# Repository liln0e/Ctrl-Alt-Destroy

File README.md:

# Ctrl+Alt+Destroy

<p align="center">
  <b>BattleBot de tipo sumo diseñado y construido por el equipo Ctrl+Alt+Destroy</b><br>
  Grado en Robótica · Escola Politécnica Superior de Enxeñaría (EPSE) · USC<br>
  Asignatura: <a href="https://www.usc.gal/es/estudios/grados/ingenieria-arquitectura/grado-robotica-2a-edicion/20252026/tecnologia-electrica-19946-19042-2-105699">Tecnología eléctrica</a>
</p>

<p align="center">
  <a href="https://www.youtube.com/live/FVRY-8WoZKk">▶ Ver la batalla</a> ·
  <a href="https://liln0e.github.io/Ctrl-Alt-Destroy/">Web del proyecto</a> ·
  <a href="https://battlebots.robotica.gal/Ctrl-Alt-Destroy/">Web oficial (battlebots.robotica.gal)</a>
</p>

---

## Descripción

**Ctrl+Alt+Destroy** es un robot BattleBot desarrollado como proyecto de la asignatura **Tecnología eléctrica** del Grado en Robótica. Junta electrónica, modelado e impresión 3D, programación y documentación técnica en un robot funcional que compitió en el torneo de la asignatura.

- **Electrónica:** PCB propia diseñada en KiCad, con una ESP32 como controlador principal.
- **Mecánica:** chasis y tapa modelados e impresos en 3D.
- **Software:** código Arduino para el control de motores, la lectura de sensores y la lógica de combate.
- **Documentación:** web hecha con Jekyll, con documentación técnica, costes y fotos del proceso.

## Estructura del repositorio

```txt
Ctrl-Alt-Destroy/
├── README.md
├── LICENSE
├── electronica/   → Esquemático y PCB en KiCad
├── mecanica/      → Modelos 3D (.3mf) y G-code del chasis y la tapa
├── software/      → Código del robot (sumo_robot_final.ino)
└── web/           → Web de documentación (Jekyll)
```

Documentación detallada en la web:

- [Documentación técnica](web/documentacion.md)
- [Costes](web/costes.md)
- [Fotos del proceso](web/fotos.md)

## Equipo

| Integrante | Rol |
|---|---|
| **Carmen Sestelo Arias** · [@carmensesteloarias](https://github.com/carmensesteloarias) | Electrónica, diseño de la PCB, código y construcción del robot |
| **Brais Maciñeiras Pena** · [@braisiiito](https://github.com/braisiiito) | Modelado e impresión 3D del chasis, código y coordinación |
| **Noelia Castro Rodríguez** · [@liln0e](https://github.com/liln0e) | Repositorio, web, documentación y decoración del robot |

## Ver la web en local

```bash
bundle install
bundle exec jekyll serve --source web
```

## Licencia

Proyecto académico publicado bajo la [licencia MIT](./LICENSE).

## Sobre este repositorio

Esta es una copia del repositorio oficial del equipo, que está en GitLab (`epse-usc/Ctrl-Alt-Destroy`), con su historial completo. Aquí la web se publica en GitHub Pages con [`.github/workflows/pages.yml`](.github/workflows/pages.yml). El archivo `.gitlab-ci.yml` se mantiene porque es el que usa el repositorio oficial.

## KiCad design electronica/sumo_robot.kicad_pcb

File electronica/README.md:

# Diseño electrónico del robot

En esta carpeta se incluye la documentación electrónica necesaria para el desarrollo del robot BattleBot del equipo **Ctrl+Alt+Destroy**.

## Contenido

Los siguientes archivos corresponden al diseño electrónico realizado en **KiCad**:

- `sumo_robot.kicad_sch` → Esquemático electrónico del circuito.
- `sumo_robot.kicad_pcb` → Diseño de la PCB del robot.
- `sumo_robot.kicad_pro` → Archivo del proyecto de KiCad.

## Diseño electrónico

La PCB ha sido diseñada para integrar los componentes electrónicos necesarios para el funcionamiento del robot, incluyendo:

- Alimentación del sistema.
- Integración del microcontrolador ESP32.
- Conexiones para sensores.
- Control de actuadores y elementos electrónicos del robot.

El diseño electrónico se ha realizado utilizando **KiCad**, permitiendo la organización de conexiones, distribución de componentes y fabricación de una PCB personalizada.

Las imágenes del diseño de la PCB y de la placa fabricada pueden consultarse en la documentación web del proyecto.

**Responsable principal:** Carmen Sestelo Arias.

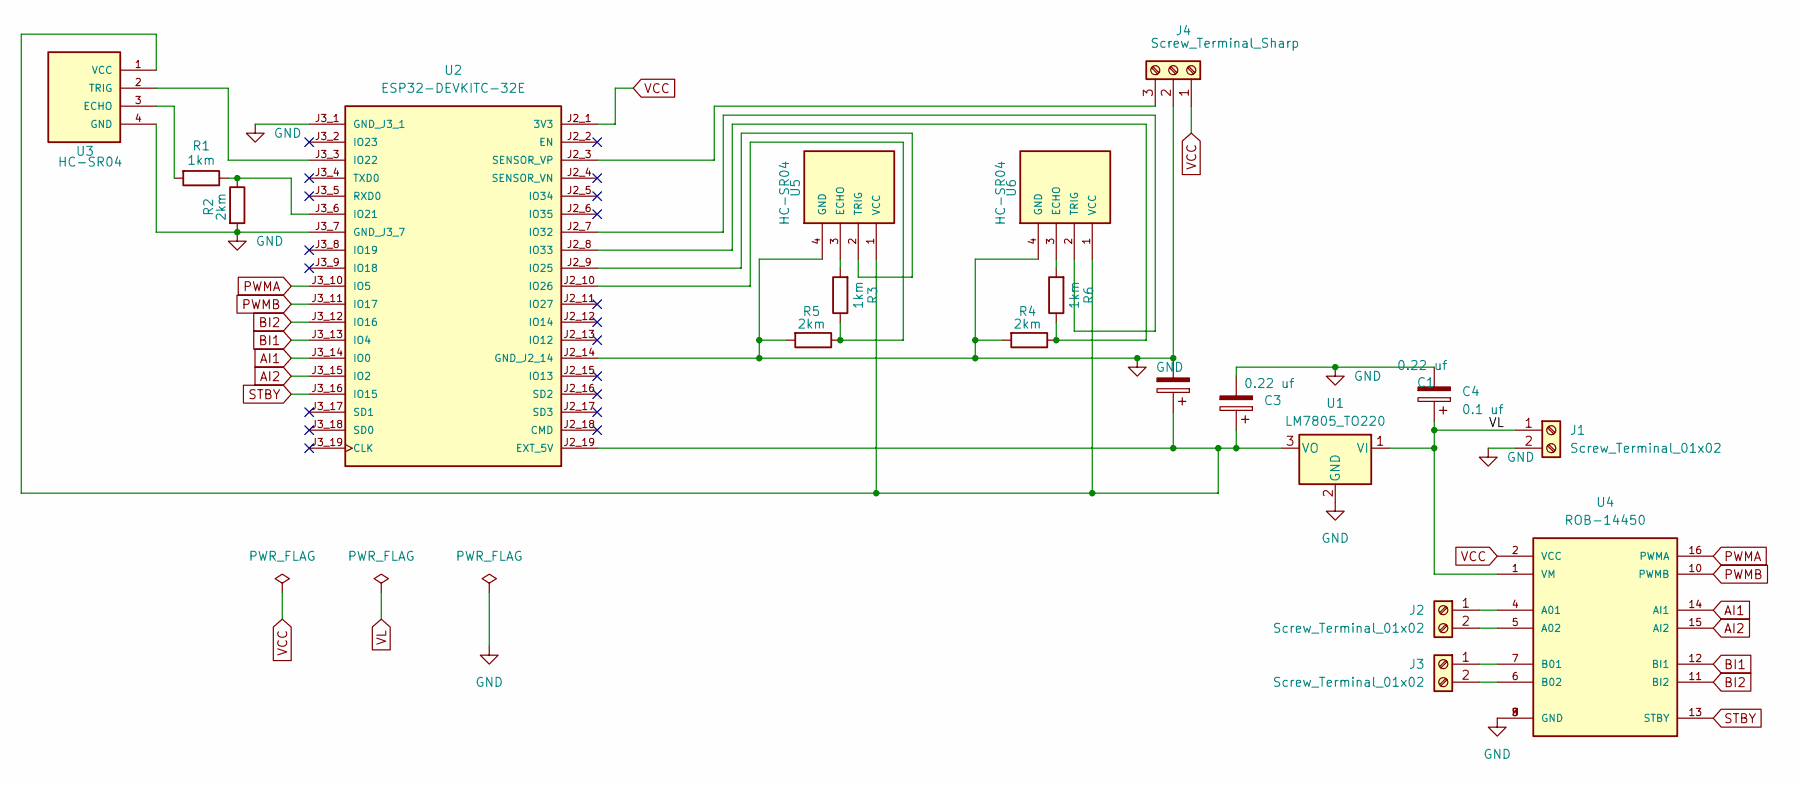
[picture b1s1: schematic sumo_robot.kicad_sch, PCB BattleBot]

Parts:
C1, C3: 0.22 uf; CP_Radial_D5.0mm_P2.50mm
C4: 0.1 uf; CP_Radial_D5.0mm_P2.50mm
J1, J2, J3: Screw_Terminal_01x02; TerminalBlock_Phoenix_MKDS-1,5-2_1x02_P5.00mm_Horizontal
J4: Screw_Terminal_Sharp; TerminalBlock_Phoenix_MKDS-1,5-3-5.08_1x03_P5.08mm_Horizont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
R1, R3, R6: 1km; R_Axial_DIN0204_L3.6mm_D1.6mm_P7.62mm_Horizontal
R2, R4, R5: 2km; R_Axial_DIN0204_L3.6mm_D1.6mm_P7.62mm_Horizontal
U1: LM7805_TO220; TO-220-3_Vertical
U2: ESP32-DEVKITC-32E; MODULE_ESP32-DEVKITC-32E; PARTREV 1.4
U3, U5, U6: HC-SR04; PinHeader_1x04_P2.54mm_Vertical
U4: ROB-14450; MODULE_ROB-14450; PARTREV 11-13-17

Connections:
AI1: U2.J3_14 (IO0), U4.14 (AI1)
AI2: U2.J3_15 (IO2), U4.15 (AI2)
BI1: U2.J3_13 (IO4), U4.12 (BI1)
BI2: U2.J3_12 (IO16), U4.11 (BI2)
GND: C1.2, C3.2, C4.2, J1.2, J4.2, R2.2, R4.2, R5.2, U1.2 (GND), U2.J2_14 (GND_J2_14), U2.J3_1 (GND_J3_1), U2.J3_7 (GND_J3_7), U3.4 (GND), U4.3 (GND), U4.8 (GND), U4.9 (GND), U5.4 (GND), U6.4 (GND)
unnamed: J2.1, U4.4 (A01)
unnamed: J2.2, U4.5 (A02)
unnamed: J3.1, U4.7 (B01)
unnamed: J3.2, U4.6 (B02)
unnamed: J4.3, U2.J2_3 (SENSOR_VP)
unnamed: C1.1, C3.1, U1.3 (VO), U2.J2_19 (EXT_5V), U3.1 (VCC), U5.1 (VCC), U6.1 (VCC)
unnamed: R1.1, R2.1, U2.J3_6 (IO21)
unnamed: U2.J3_3 (IO22), U3.2 (TRIG)
unnamed: U2.J2_9 (IO25), U5.2 (TRIG)
unnamed: R3.1, R5.1, U2.J2_10 (IO26)
unnamed: U2.J2_7 (IO32), U6.2 (TRIG)
unnamed: R4.1, R6.1, U2.J2_8 (IO33)
unnamed: R1.2, U3.3 (ECHO)
unnamed: R3.2, U5.3 (ECHO)
unnamed: R6.2, U6.3 (ECHO)
PWMA: U2.J3_10 (IO5), U4.16 (PWMA)
PWMB: U2.J3_11 (IO17), U4.10 (PWMB)
STBY: U2.J3_16 (IO15), U4.13 (STBY)
VCC: J4.1, U2.J2_1 (3V3), U4.2 (VCC)
VL: C4.1, J1.1, U1.1 (VI), U4.1 (VM)

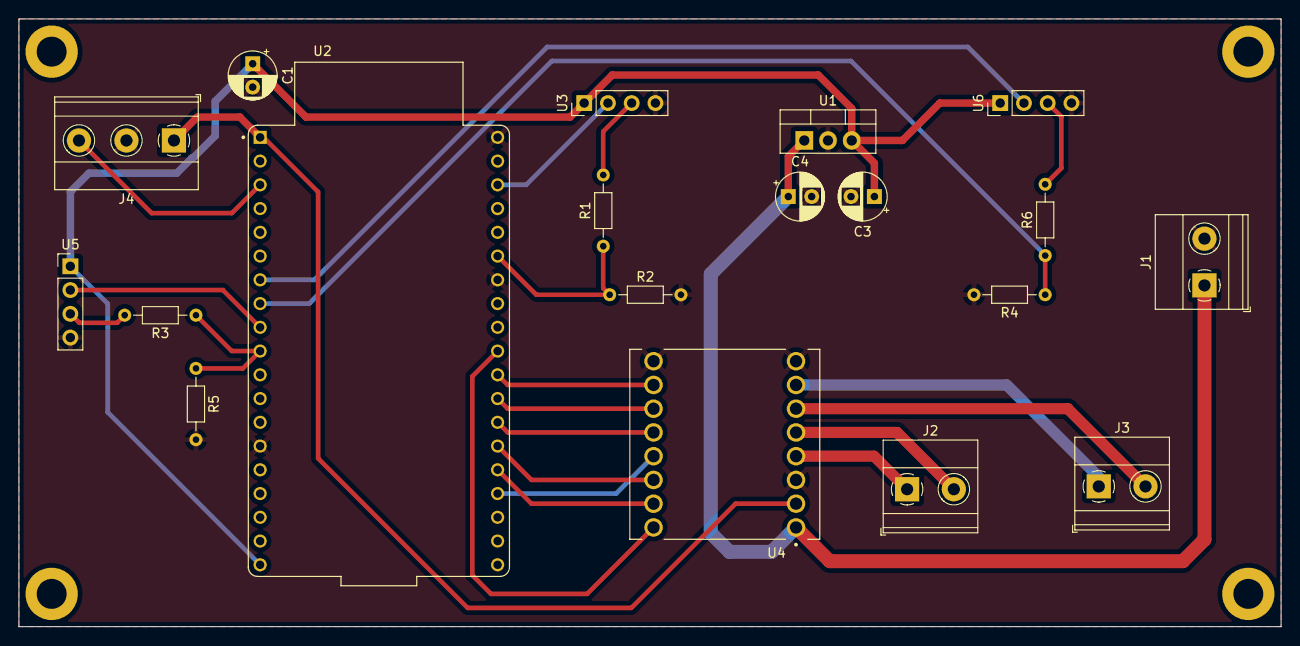
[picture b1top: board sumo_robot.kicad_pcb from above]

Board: 2 copper layers, 135.0 x 65.0 mm, 19 parts (0 on the bottom side), 25 nets.

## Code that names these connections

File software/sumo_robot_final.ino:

#include <Arduino.h>

#define TRIG_FRONT   22
#define ECHO_FRONT   21
#define TRIG_LEFT    32
#define ECHO_LEFT    33
#define TRIG_RIGHT   25
#define ECHO_RIGHT   26

#define LINE_SENSOR  34

#define STBY   15
#define PWMA    5
#define AIN1    0
#define AIN2    2
#define PWMB   17
#define BIN1    4
#define BIN2   16

const bool INVERT_MOTOR_A = true;
const bool INVERT_MOTOR_B = true;

const bool INVERT_LINEA_LOGICA = false;

//parametros
const int VEL_BUSCAR    =  90;
const int VEL_ATACAR    = 120;
const int VEL_RETROCESO = 120;
const int VEL_GIRO_FUGA = 120;

const float DIST_DETECCION = 80.0;
const float DIST_TIMEOUT   = 400.0;

const unsigned long ESPERA_INICIAL_MS = 5000;
const unsigned long T_RETROCESO_MS    = 250;
const unsigned long T_GIRO_FUGA_MS    = 300;

const bool ACTIVAR_DETECCION_LINEA = true;

//estado
enum Estado { ESPERANDO, BUSCANDO, ATACANDO, FUGA_RETROCESO, FUGA_GIRO };
Estado estado = ESPERANDO;

unsigned long t_inicio_estado = 0;
int  ultimo_giro = +1;

float medirDistancia(int trigPin, int echoPin);
void  motorA(int velocidad);
void  motorB(int velocidad);
void  pararMotores();
void  avanzar(int v);
void  retroceder(int v);
void  girarDerecha(int v);
void  girarIzquierda(int v);
bool  veLineaBlanca();

void setup() {
  Serial.begin(115200);
  delay(100);
  Serial.println(F("\n=== SUMO ROBOT v7 FINAL ==="));

  pinMode(TRIG_FRONT, OUTPUT);  pinMode(ECHO_FRONT, INPUT);
  pinMode(TRIG_LEFT,  OUTPUT);  pinMode(ECHO_LEFT,  INPUT);
  pinMode(TRIG_RIGHT, OUTPUT);  pinMode(ECHO_RIGHT, INPUT);
  digitalWrite(TRIG_FRONT, LOW);
  digitalWrite(TRIG_LEFT,  LOW);
  digitalWrite(TRIG_RIGHT, LOW);

  pinMode(LINE_SENSOR, INPUT);

  pinMode(STBY, OUTPUT);
  pinMode(PWMA, OUTPUT); pinMode(AIN1, OUTPUT); pinMode(AIN2, OUTPUT);
  pinMode(PWMB, OUTPUT); pinMode(BIN1, OUTPUT); pinMode(BIN2, OUTPUT);

  digitalWrite(STBY, LOW);
  pararMotores();

  Serial.println(F("Esperando 5 segundos..."));
  unsigned long t0 = millis();
  while (millis() - t0 < ESPERA_INICIAL_MS) {
    Serial.printf("  %lu ms\n", millis() - t0);
    delay(500);
  }

  digitalWrite(STBY, HIGH);
  estado = BUSCANDO;
  t_inicio_estado = millis();
  Serial.println(F("¡Empieza el combate!"));
}

void loop() {
  if (ACTIVAR_DETECCION_LINEA && veLineaBlanca() && estado != ESPERANDO) {
    Serial.println(F("¡LINEA BLANCA!"));
    estado = FUGA_RETROCESO;
    t_inicio_estado = millis();
  }

  //lectura de distancias
  float dF = medirDistancia(TRIG_FRONT, ECHO_FRONT);
  float dL = medirDistancia(TRIG_LEFT,  ECHO_LEFT);
  float dR = medirDistancia(TRIG_RIGHT, ECHO_RIGHT);

  //maquina de estados
  switch (estado) {

    case BUSCANDO: {
      bool vF = (dF > 2 && dF < DIST_DETECCION);
      bool vL = (dL > 2 && dL < DIST_DETECCION);
      bool vR = (dR > 2 && dR < DIST_DETECCION);

      if (vF || vL || vR) {
        estado = ATACANDO;
        t_inicio_estado = millis();
      } else {
        if (ultimo_giro >= 0) girarDerecha(VEL_BUSCAR);
        else                  girarIzquierda(VEL_BUSCAR);
      }
    } break;

    case ATACANDO: {
      float menor = DIST_TIMEOUT;
      char dir = 'F';
      if (dF > 2 && dF < menor) { menor = dF; dir = 'F'; }
      if (dL > 2 && dL < menor) { menor = dL; dir = 'L'; }
      if (dR > 2 && dR < menor) { menor = dR; dir = 'R'; }

      if (menor >= DIST_DETECCION) {
        estado = BUSCANDO;
        t_inicio_estado = millis();
        break;
      }

      switch (dir) {
        case 'F':
          avanzar(VEL_ATACAR);
          break;
        case 'L':
          motorA(VEL_ATACAR / 3);
          motorB(VEL_ATACAR);
          ultimo_giro = -1;
          break;
        case 'R':
          motorA(VEL_ATACAR);
          motorB(VEL_ATACAR / 3);
          ultimo_giro = +1;
          break;
      }
    } break;

    case FUGA_RETROCESO: {
      retroceder(VEL_RETROCESO);
      if (millis() - t_inicio_estado > T_RETROCESO_MS) {
        estado = FUGA_GIRO;
        t_inicio_estado = millis();
        ultimo_giro = -ultimo_giro;
      }
    } break;

    case FUGA_GIRO: {
      if (ultimo_giro >= 0) girarDerecha(VEL_GIRO_FUGA);
      else                  girarIzquierda(VEL_GIRO_FUGA);
      if (millis() - t_inicio_estado > T_GIRO_FUGA_MS) {
        estado = BUSCANDO;
        t_inicio_estado = millis();
      }
    } break;

    default: break;
  }

  static unsigned long t_last_print = 0;
  if (millis() - t_last_print > 200) {
    t_last_print = millis();
    int line_d = digitalRead(LINE_SENSOR);
    bool blanco = veLineaBlanca();
    Serial.printf("E=%d  F=%5.1f  L=%5.1f  R=%5.1f  line=%d  -> %s\n",
                  estado, dF, dL, dR, line_d, blanco ? "BLANCO" : "NEGRO");
  }
}


float medirDistancia(int trigPin, int echoPin) {
  digitalWrite(trigPin, LOW);
  delayMicroseconds(3);
  digitalWrite(trigPin, HIGH);
  delayMicroseconds(10);
  digitalWrite(trigPin, LOW);
  unsigned long dur = pulseIn(echoPin, HIGH, 25000UL);
  if (dur == 0) return DIST_TIMEOUT;
  return dur * 0.0343f / 2.0f;
}

bool veLineaBlanca() {
  int v = digitalRead(LINE_SENSOR);
  bool blanco = (v == LOW);
  if (INVERT_LINEA_LOGICA) blanco = !blanco;
  return blanco;
}

void motorA(int v) {
  if (INVERT_MOTOR_A) v = -v;
  v = constrain(v, -255, 255);
  if (v >= 0) {
    digitalWrite(AIN1, HIGH); digitalWrite(AIN2, LOW);
    analogWrite(PWMA, v);
  } else {
    digitalWrite(AIN1, LOW);  digitalWrite(AIN2, HIGH);
    analogWrite(PWMA, -v);
  }
}

void motorB(int v) {
  if (INVERT_MOTOR_B) v = -v;
  v = constrain(v, -255, 255);
  if (v >= 0) {
    digitalWrite(BIN1, HIGH); digitalWrite(BIN2, LOW);
    analogWrite(PWMB, v);
  } else {
    digitalWrite(BIN1, LOW);  digitalWrite(BIN2, HIGH);
    analogWrite(PWMB, -v);
  }
}

void pararMotores() {
  motorA(0); motorB(0);
  digitalWrite(AIN1, HIGH); digitalWrite(AIN2, HIGH); analogWrite(PWMA, 0);
  digitalWrite(BIN1, HIGH); digitalWrite(BIN2, HIGH); analogWrite(PWMB, 0);
}

void avanzar(int v)        { motorA( v);  motorB( v); }
void retroceder(int v)     { motorA(-v);  motorB(-v); }
void girarDerecha(int v)   { motorA( v);  motorB(-v); }
void girarIzquierda(int v) { motorA(-v);  motorB( v); }

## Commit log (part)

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2026-04-25 proyecto de KiCad
2026-05-11 Upload New File
2026-05-11 Add new directory
2026-05-11 Edit DOCUMENTACION.md
2026-05-11 Edit README.md
2026-05-11 Edit .gitkeep
2026-05-11 Edit index.md
2026-05-11 Edit fotos.md
2026-05-11 Edit README-ORIGINAL.md
2026-05-11 Edit costes.md
2026-05-12 Edit _config.yml
